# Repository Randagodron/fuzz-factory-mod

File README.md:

# fuzz-factory-mod
Heavily modified Fuzz Factory

Stompbox for electric guitar, based on the Fuzz Factory from ZVex, with digital control, HMI, preset memorisation and more.

This circuit is an experimentation platform around the Fuzz Face / Tonebender fuzz circuits.

# HW features

* Full-analog audio path, with digital control through digipots and VCAs
* Mono audio input and output, expression pedal input, MIDI in / out
* Standard stompbox DC power supply (9V, positive ring) + 9V battery
* 3 push button footwitches
* Multi-PCB, modular design with separated PCB for HMI and core audio circuit for future customisation
* Mechanical mounting through pots and audio connectors
* 4-Layer class 5 PCB for main board, 2-layer class 4 for HMI and audio circuit
* ...

# SW features

* STM32F303 MCU
* Preset memorisation via rolling EEPROM emulation inside MCU Flash memory
* MIDI support
* ...

# Contents

* Circuit CAD : Kicad
* Mechanics : FreeCAD
* Simulation : LTSpice
* SW : STM32CubeIDE

# Directory structure

* /cad : Kicad files
* /sim : electronics simulation files
* /mec : mechanical files
* /sw : software files
* /export : binaries and Kicad outputs

# Companion articles (in french)

http://blog.randagodron.eu/index.php?post/2019/05/26/Fuzzquest-Episode-2  
http://blog.randagodron.eu/index.php?post/2020/02/14/Fuzzquest-Episode-3  
http://blog.randagodron.eu/index.php?post/2020/03/26/Fuzzquest-Episode-4

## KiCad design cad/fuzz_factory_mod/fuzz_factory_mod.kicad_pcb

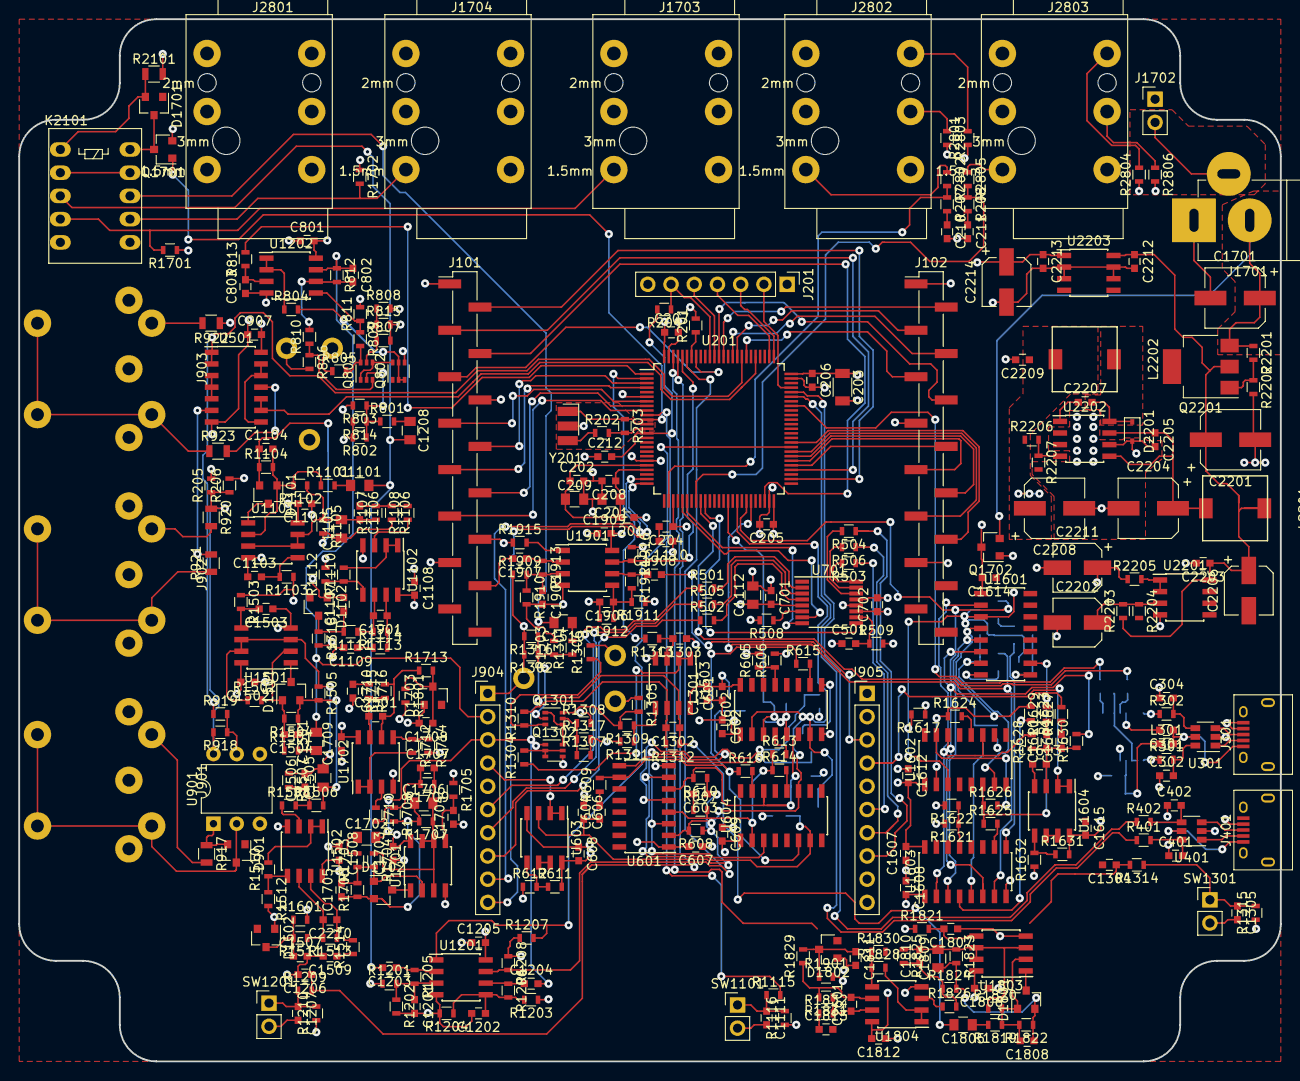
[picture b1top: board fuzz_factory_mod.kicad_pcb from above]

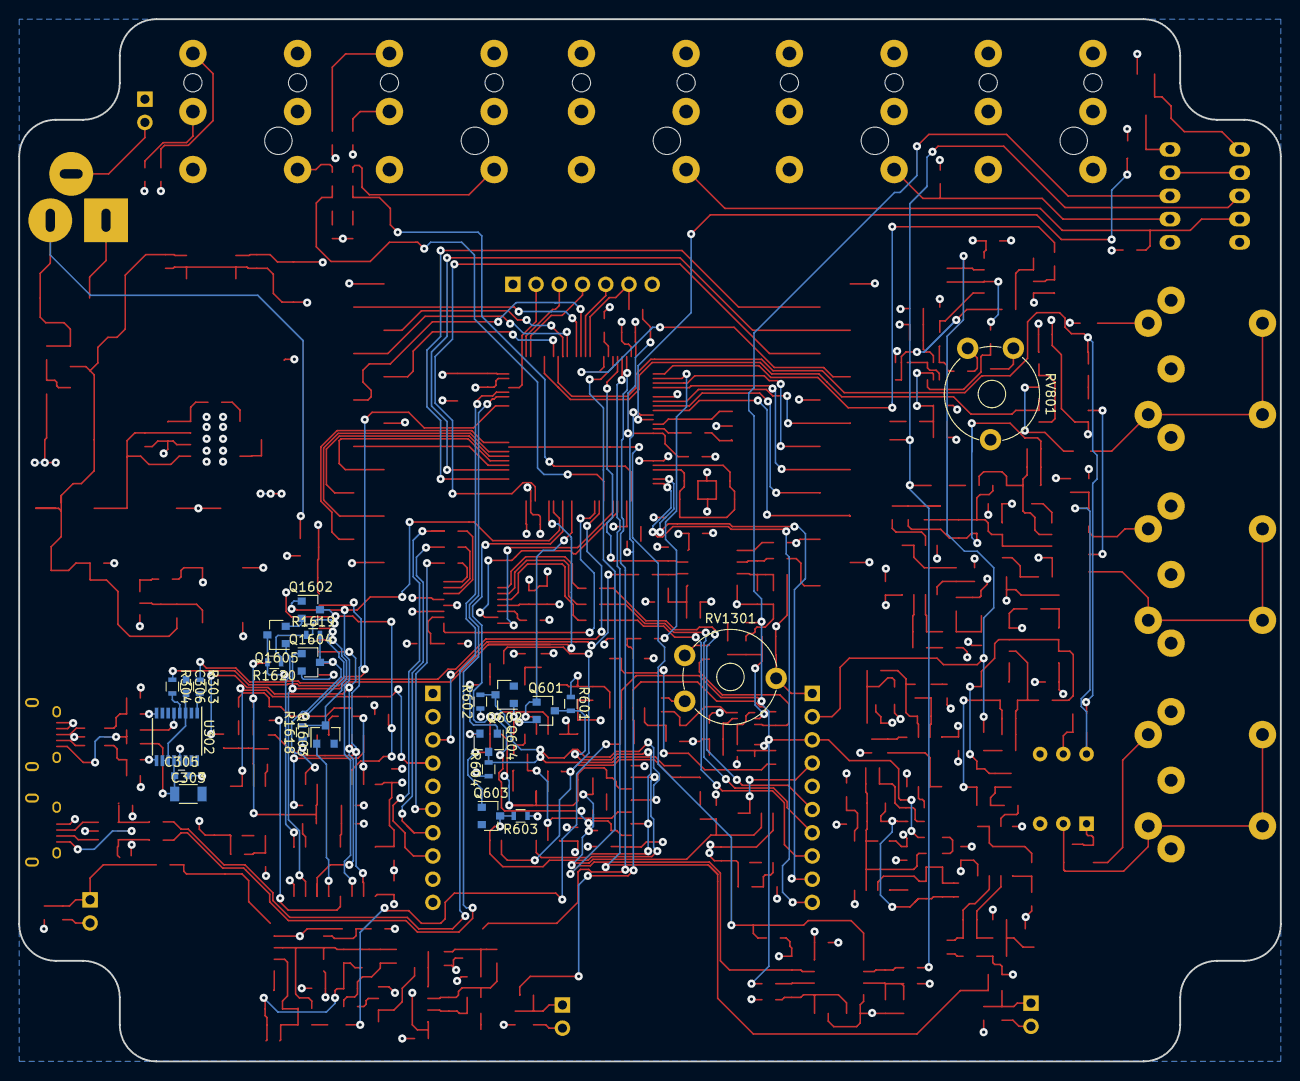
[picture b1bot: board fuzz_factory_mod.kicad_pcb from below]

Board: 4 copper layers, 138.0 x 114.0 mm, 388 parts (23 on the bottom side), 268 nets.

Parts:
C201, C209, C1101, C1112, C1208, C1501, C1510, C1702, C1805: 1u; C_0805
C202, C208, C301: 10n; C_0603
C203, C303: 4u7; C_1206
C204, C205, C206, C207, C210, C211, C212, C305, C306, C501, C601, C602, C603, C604, C606, C607, C608, C609, C701, C702, C801, C803, C907, C1102, C1103, C1104, C1106, C1107, C1108, C1109, C1110, C1111, C1201, C1202, C1203, C1204, C1205, C1206, C1207, C1301, C1303, C1304, C1305, C1502, C1503, C1504, C1506, C1507, C1508, C1509, C1607, C1608, C1609, C1610, C1612, C1613, C1614, C1615, C1703, C1704, C1705, C1707, C1708, C1709, C1710, C1806, C1807, C1808, C1810, C1811, C1812, C1813, C1905, C1906, C1907, C1908, C1909: 100n; C_0603
C302, C304, C401, C402: 47p; C_0603
C802, C1302, C1901, C2210, C2501, C2601: 100p; C_0603
C1105, C1505, C1706, C1809: 220n; C_0805
C1701, C2201, C2204, C2208: 100uF/25V; CP_Elec_6.3x4.5
C2202, C2206, C2211, C2214: 10u; CP_Elec_5x5.8
C2203, C2205, C2209, C2212, C2213: 100nF; C_0603
C2207: 10nF; C_0603
D901: BAT54A; SOT-23
D1101, D1501, D1701, D1702, D1801: BAV23S; SOT-23
D1102, D1502, D1703, D1802: BZX84Cxx; D_SOT-23_ANK
D2201: BAS3010B; D_SOD-323
J101: Conn_interface_1; Pin_Header_Straight_1x16_Pitch2.54mm_SMD_Pin1Left
J102: Conn_interface_2; Pin_Header_Straight_1x16_Pitch2.54mm_SMD_Pin1Left
J201: Conn_MCU_SWD; Pin_Header_Straight_1x07_Pitch2.54mm
J301, J401: USB_B_Micro; USB_Micro-B
J901: CONN_MIDI_IN; DIN5_through_hole
J902: CONN_MIDI_THRU; DIN5_through_hole
J903: CONN_MIDI_OUT; DIN5_through_hole
J904, J905: Conn_01x10_Female; Pin_Header_Straight_1x10_Pitch2.54mm
J1701: Barrel_Jack_Switch; JACK_ALIM
J1702: Conn_Battery; Pin_Header_Straight_1x02_Pitch2.54mm
J1703: CONN_AUDIO_IN; CLIFF_FCR5005x
J1704: CONN_AUDIO_OUT; CLIFF_FCR5005x
J2801: CONN_AUDIO_OUT_REF; CLIFF_FCR5005x
J2802: CONN_EXP_1; CLIFF_FCR5005x
J2803: CONN_EXP_2; CLIFF_FCR5005x
K2101: Fujitsu-Takamisawa-A_AL; Relay_DPDT_FRT5
L201: BLMxxx; C_0603
L301: L_Core_Ferrite_Small; C_0603
L2201, L2202: 100u; L_TDK_SLF7045
Q601, Q602, Q603, Q604, Q1602, Q1603, Q1604, Q1605: DTA123Y; SOT-23
Q801, Q802, Q1301, Q1302: MMDT3904; SOT-363_SC-70-6
Q1701: DTC114Y; SOT-23
Q1702: DTA114E; SOT-23
Q2201: BCP51; SOT-223
R201, R509, R611, R612, R803, R804, R808, R813, R814, R815, R1102, R1103, R1105, R1106, R1108, R1110, R1111, R1112, R1113, R1114, R1116, R1210, R1303, R1304, R1308, R1313, R1315, R1316, R1317, R1318, R1502, R1503, R1505, R1506, R1508, R1510, R1511, R1512, R1513, R1514, R1601, R1631, R1632, R1704, R1705, R1707, R1708, R1710, R1712, R1713, R1714, R1715, R1716, R1801, R1820, R1821, R1823, R1824, R1826, R1828, R1829, R1830, R1831, R1832, R1901, R2201, R2202, R2203, R2204: 10k; R_0603
R202: 390; R_0603
R203, R607, R608, R801, R1301, R1627, R1628, R1701, R1702: 1M; R_0603
R204, R205, R206, R501, R502, R503, R504, R505, R506, R508, R605, R606, R613, R614, R615, R616, R1621, R1622, R1623, R1624, R1625, R1626: 0; R_0603
R207, R208, R919, R1115, R1209, R1314, R2205: 100; R_0603
R301, R302, R303, R304, R401, R402: 27; R_0603
R601, R602, R603, R604, R918, R1201, R1202, R1203, R1204, R1617, R1618, R1619, R1620, R1909, R1910, R1911, R1912: 4k7; R_0603
R609, R610, R1629, R1630: 3k9; R_0603
R802, R807, R809, R810, R811, R812, R1104, R1107, R1205, R1206, R1302, R1307, R1309, R1310, R1311, R1312, R1504, R1507, R1706, R1709, R1822, R1825, R1913, R1914: 100k; R_0603
R805, R806, R1305, R1306: 330; R_0603
R917, R920, R921, R922, R923: 220; R_0805
R1101, R1207, R1208, R1501, R1703, R1819, R1915, R1916, R2801, R2802, R2803, R2804, R2805, R2806: 1k; R_0603
R2101: 200; R_0805
R2206: 82k; R_0603
R2207: 47k; R_0603
RV801, RV1301: R_POT_TRIM; Potentiometer_Trimmer_Piher_PT-10v10_Horizontal_Px10.0mm_Py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
SW1101, SW1201, SW1301: SW_PUSH; Pin_Header_Straight_1x02_Pitch2.54mm
U201: STM32F303VCTx; LQFP-100_14x14mm_Pitch0.5mm
U301, U401: USBLC6-2SC6; SOT-23-6
U302: FT230XS; SSOP-16_3.9x4.9mm_Pitch0.635mm
U501: 74LS132; SOIC-14_3.9x8.7mm_Pitch1.27mm
U601, U1601: 4050; SOIC-16_3.9x9.9mm_Pitch1.27mm
U602, U1603: 4504; SOIC-16_3.9x9.9mm_Pitch1.27mm
U603, U1102, U1202, U1502, U1503, U1604, U1702, U1804: MC33202; SOIC-8_3.9x4.9mm_Pitch1.27mm
U604, U1602: 4049; SOIC-16_3.9x9.9mm_Pitch1.27mm
U701: AD5262_ABC; TSSOP-16_4.4x5mm_Pitch0.65mm
U901: 4N25; DIP-6_W7.62mm
U1101, U1501, U1701, U1803: LM1458; SOIC-8_3.9x4.9mm_Pitch1.27mm
U1201, U1901: LM2903; SOIC-8_3.9x4.9mm_Pitch1.27mm
U2201: TL072; SOIC-8_3.9x4.9mm_Pitch1.27mm
U2202: LM2674M-ADJ; SOIC-8_3.9x4.9mm_Pitch1.27mm
U2203: LM78L05_SO8; SOIC-8_3.9x4.9mm_Pitch1.27mm
Y201: Resonator_Small; Resonator_AEL_ZTTxx_SMD

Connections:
+3.3VA: C201.1, C202.1, C208.1, C209.1, L201.2, U201.21, U201.22
+3V3: C203.1, C204.1, C205.1, C206.1, C207.1, C602.2, C702.2, C1608.2, C2208.1, C2209.1, J101.12, J102.7, J201.1, L201.1, L2202.2, R205.2, R508.2, R509.2, R605.2, R1116.1, R1207.1, R1208.1, R1210.1, R1315.1, R1621.2, R1915.1, R1916.1, R2206.1, R2801.1, R2804.1, U201.6, U201.28, U201.50, U201.75, U201.100, U602.1, U701.13, U1603.1
+5V: C2213.1, C2214.1, J101.6, R206.2, U2203.1
+9V: C601.2, C607.2, C608.2, C609.2, C701.2, C801.2, C1102.2, C1108.2, C1112.1, C1205.2, C1301.2, C1502.2, C1508.2, C1607.2, C1612.2, C1614.2, C1615.2, C1703.2, C1709.2, C1806.2, C1812.2, C1909.2, J904.1, J905.1, Q1702.3, R601.1, R602.1, R603.1, R604.1, R611.2, R802.2, R807.2, R811.2, R814.2, R815.2, R1201.1, R1203.1, R1302.2, R1307.2, R1311.2, R1316.2, R1317.2, R1318.2, R1601.2, R1617.1, R1618.1, R1619.1, R1620.1, R1631.2, R1801.2, R1901.2, R1909.1, R1911.1, RV801.2, RV1301.2, U601.1, U602.16, U603.8, U604.1, U701.5, U1101.8, U1102.8, U1201.8, U1202.8, U1501.8, U1502.8, U1503.8, U1601.1, U1602.1, U1603.16, U1604.8, U1701.8, U1702.8, U1803.8, U1804.8, U1901.8
+BATT: C1701.1, J1701.2, Q1702.2, Q2201.3, R2101.2, R2201.1
/ANALOG/DAC/IN_PWM_LSB_BUFF: R608.2, U601.2, U602.2, U604.11
/ANALOG/DAC/IN_PWM_LSBn: Q602.1, U602.5
/ANALOG/DAC/IN_PWM_LSBn_BUFF: R607.2, R613.1, R614.1, U601.4, U604.2
/ANALOG/DAC/IN_PWM_MSB_BUFF: R610.2, U601.6, U602.6, U604.14
/ANALOG/DAC/IN_PWM_MSBn: Q604.1, U602.9
/ANALOG/DAC/IN_PWM_MSBn_BUFF: R609.2, R615.1, R616.1, U601.10, U604.6
/ANALOG/DAC_CMD: J904.4, U603.1, U603.2
/ANALOG/DAC_CMD_REF: J905.4, U1604.1, U1604.2
/ANALOG/DAC_REF/IN_PWM_LSB_BUFF: R1628.2, U1601.2, U1602.11, U1603.2
/ANALOG/DAC_REF/IN_PWM_LSBn: Q1603.1, U1603.5
/ANALOG/DAC_REF/IN_PWM_LSBn_BUFF: R1623.1, R1624.1, R1627.2, U1601.4, U1602.2
/ANALOG/DAC_REF/IN_PWM_MSB_BUFF: R1630.2, U1601.6, U1602.14, U1603.6
/ANALOG/DAC_REF/IN_PWM_MSBn: Q1605.1, U1603.9
/ANALOG/DAC_REF/IN_PWM_MSBn_BUFF: R1625.1, R1626.1, R1629.2, U1601.10, U1602.6
/ANALOG/Digipot/POT1_1: R501.2, U701.2
/ANALOG/Digipot/POT1_2: R505.2, U701.3
/ANALOG/Digipot/POT1_3: R502.2, U701.4
/ANALOG/Digipot/POT2_1: R503.2, U701.16
/ANALOG/Digipot/POT2_2: R506.2, U701.15
/ANALOG/Digipot/POT2_3: R504.2, U701.14
/ANALOG/Digipot/~DIGIPOT_PR: C501.2, R509.1, U701.10
/ANALOG/Digipot/~DIGIPOT_SHDN: R508.1, U701.6
/ANALOG/GAIN_POT_1: J904.6, R501.1
/ANALOG/GAIN_POT_2: J904.7, R505.1
/ANALOG/GAIN_POT_3: J904.8, R502.1
/ANALOG/GAIN_POT_REF_1: J905.6, R503.1
/ANALOG/GAIN_POT_REF_2: J905.7, R506.1
/ANALOG/GAIN_POT_REF_3: J905.8, R504.1
/ANALOG/IN_AUDIO_PEAK: C1109.1, R1114.1
/ANALOG/IN_AUDIO_VCA: C802.1, C1501.2, J904.2, R812.1, U1202.7
/ANALOG/IN_AUDIO_VCA_PEAK: C1509.1, R1514.1
/ANALOG/OUT_AUDIO_PEAK: C1710.1, R1716.1
/ANALOG/OUT_AUDIO_REF: C1908.2, J905.3
/ANALOG/OUT_AUDIO_VCA_PEAK: C1813.1, R1832.1
/ANALOG/VCA_IN/CV: C803.2, R813.1, U1202.3
/ANALOG/VCA_OUT/CV: C1303.2, R1313.1, U1503.3
/ANALOG/freq_meas_ref/OUT_1: R1915.2, U1901.1
/ANALOG/peak_detect_audio_in/Vsub: C1107.1, D1102.1, R1111.2, R1318.1
/ANALOG/peak_detect_in_audio_vca/Vsub: C1507.1, D1502.1, R1511.2, R1601.1
/ANALOG/peak_detect_out_audio/Vsub: C1708.1, D1703.1, R1713.2, R1801.1
/ANALOG/peak_detect_out_audio_vca/Vsub: C1811.1, D1802.1, R1829.2, R1901.1
/CONNECTORS/AUDIO_IN_CONN: J1703.3, K2101.4, R1701.2
/CONNECTORS/AUDIO_OUT_CONN: J1704.3, K2101.7, R1702.2
/MCU/JNTRST: J201.6, R204.1, U201.90
/MCU/JTCK_SWCLK: J201.3, U201.76
/MCU/JTDI: J201.4, U201.77
/MCU/JTDO_TRACESWO: J201.5, U201.89
/MCU/JTMS_SWDIO: J201.2, U201.72
/MCU/MIDI/+5V_IN: C907.2, R205.1, R206.1, R918.2, R920.1, R922.1, U501.14, U901.6
/MCU/NRST: C212.2, R204.2, U201.14
/MCU/SW_BYPASS: C1110.1, R1115.2, U201.10
/MCU/SW_PRESET_DOWN: C1304.1, R1314.2, U201.98
/MCU/SW_PRESET_UP: C1206.1, R1209.2, U201.97
/MCU/UART5_RX: R919.1, U201.83, U501.1, U501.2
/MCU/UART5_TX: U201.80, U501.9, U501.10
/MCU/USART1_RX: R304.1, U201.34
/MCU/USART1_TX: R303.1, U201.68
/MCU/USB_UART/VBUS: C303.1, C305.1, L301.1, U302.12
/PSU/DCDC_VSW: C2207.2, D2201.1, L2202.1, U2202.8
ADC_FF_pol1: J904.9, U201.24
ADC_FF_pol2: J904.10, U201.25
AUDIO_IN_FX: C1101.2, C1203.2, C1208.2, K2101.3
AUDIO_OUT_FX: C1204.2, C1302.1, C1510.2, C1702.2, C1805.2, J904.3, K2101.8, R1312.1, U1503.7
BYPASS_CMD: Q1701.1, U201.11
DISP_ENABLE: J101.4, U201.48
DISP_LATCH: J101.5, U201.93
ENC1_BTN: J101.7, U201.7
ENC1_IN_CCW: J101.11, U201.9
ENC1_IN_CW: J101.10, U201.8
ENC1__LED_GREEN: J101.9, U201.4
ENC1__LED_RED: J101.8, U201.3
ENC2_BTN: J102.2, U201.87
ENC2_IN_CCW: J102.6, U201.88
ENC2_IN_CW: J102.5, U201.82
ENC2_LED_GREEN: J102.4, U201.85
ENC2_LED_RED: J102.3, U201.84
ENC3_BTN: J102.8, U201.55
ENC3_IN_CCW: J102.12, U201.60
ENC3_IN_CW: J102.11, U201.58
ENC3_LED_GREEN: J102.10, U201.57
ENC3_LED_RED: J102.9, U201.56
EXP_1: R207.1, R2802.2, U201.27
EXP_2: R208.1, R2805.2, U201.33
FF_Stab_DAC_PWM_LSB: Q601.1, U201.40, U602.3
FF_Stab_DAC_PWM_MSB: Q603.1, U201.42, U602.7
GNDA: C201.2, C202.2, C203.2, C204.2, C205.2, C206.2, C207.2, C208.2, C209.2, C210.2, C211.2, C212.1, C301.2, C302.1, C303.2, C304.1, C305.2, C306.1, C401.1, C402.1, C501.1, C601.1, C602.1, C606.1, C607.1, C608.1, C609.1, C701.1, C702.1, C801.1, C803.1, C907.1, C1102.1, C1103.1, C1107.2, C1108.1, C1109.2, C1110.2, C1111.2, C1112.2, C1201.2, C1202.2, C1205.1, C1206.2, C1207.2, C1301.1, C1303.1, C1304.2, C1305.2, C1502.1, C1503.1, C1507.2, C1508.1, C1509.2, C1607.1, C1608.1, C1612.1, C1613.1, C1614.1, C1615.1, C1701.2, C1703.1, C1704.1, C1708.2, C1709.1, C1710.2, C1806.1, C1807.1, C1811.2, C1812.1, C1813.2, C1905.2, C1906.2, C1909.1, C2201.2, C2202.2, C2203.2, C2204.2, C2205.2, C2206.2, C2208.2, C2209.2, C2211.2, C2212.2, C2213.2, C2214.2, D1102.2, D1502.2, D1703.2, D1802.2, D2201.2, J101.1, J101.13, J102.1, J102.13, J201.7, J301.4, J301.5, J301.6, J401.4, J401.5, J401.6, J902.2, J903.2, J904.5, J905.5, J1701.1, J1703.1, J1703.4, J1704.1, J1704.4, J2801.1, J2801.4, J2802.1, J2802.6, J2803.1, J2803.6, Q601.2, Q602.2, Q603.2, Q604.2, Q802.1, Q802.4, Q1302.1, Q1302.4, Q1602.2, Q1603.2, Q1604.2, Q1605.2, Q1701.2, Q1702.1, R201.2, R606.2, R612.1, R803.2, R808.2, R1112.2, R1202.2, R1204.2, R1303.2, R1308.2, R1512.2, R1622.2, R1632.1, R1701.1, R1702.1, R1714.2, R1830.2, R1910.2, R1912.2, R2202.2, R2204.2, R2207.2, R2803.2, R2806.2, SW1101.2, SW1201.2, SW1301.2, U201.20, U201.49, U201.74, U201.99, U301.2, U302.5, U302.13, U401.2, U501.7, U601.8, U602.8, U603.4, U604.8, U701.11, U701.12, U901.4, U1101.4, U1102.4, U1201.4, U1202.4, U1501.4, U1502.4, U1503.4, U1601.8, U1602.8, U1603.8, U1604.4, U1701.4, U1702.4, U1803.4, U1804.4, U1901.4, U2201.4, U2202.6, U2203.2, U2203.3, U2203.6, U2203.7, Y201.2
INPUT_CAPTURE_1: R1207.2, U201.59, U1201.1
INPUT_CAPTURE_2: R1208.2, U201.95, U1201.7
INPUT_CAPTURE_3: R1916.2, U201.96, U1901.7
unnamed: C210.1, R207.2
unnamed: C211.1, R208.2
unnamed: C301.1, J301.1, L301.2, U301.5
unnamed: C302.2, R301.2, U301.6
unnamed: C304.2, R302.2, U301.4
unnamed: C306.2, U302.3, U302.10, U302.11
unnamed: C401.2, R401.2, U401.6
unnamed: C402.2, R402.2, U401.4
unnamed: C603.1, C604.1, C606.2, R608.1, R610.1, U603.3
unnamed: C603.2, R607.1
unnamed: C604.2, R609.1
unnamed: C802.2, R810.2, R812.2, U1202.6
unnamed: C1101.1, R1101.2
unnamed: C1103.2, R1103.2, U1101.5
unnamed: C1104.1, C1105.1, D1101.2, R1104.1, R1105.2, R1106.2
unnamed: C1104.2, D1101.1, R1101.1, R1102.2, R1104.2, U1101.2
unnamed: C1105.2, C1106.2, R1102.1, R1105.1, R1107.1, U1101.3, U1101.6, U1101.7
unnamed: C1106.1, R1106.1, R1107.2, R1108.2
unnamed: C1111.1, R1115.1, R1116.2, SW1101.1
unnamed: C1201.1, R1201.2, R1202.1, R1205.2, U1201.3
unnamed: C1202.1, R1203.2, R1204.1, R1206.2, U1201.5
unnamed: C1203.1, R1205.1, U1201.2
unnamed: C1204.1, R1206.1, U1201.6
unnamed: C1207.1, R1209.1, R1210.2, SW1201.1
unnamed: C1208.1, R801.2
unnamed: C1302.2, R1310.2, R1312.2, U1503.6
unnamed: C1305.1, R1314.1, R1315.2, SW1301.1
unnamed: C1501.1, R1501.2
unnamed: C1503.2, R1503.2, U1501.5
unnamed: C1504.1, C1505.1, D1501.2, R1504.1, R1505.2, R1506.2
unnamed: C1504.2, D1501.1, R1501.1, R1502.2, R1504.2, U1501.2
unnamed: C1505.2, C1506.2, R1502.1, R1505.1, R1507.1, U1501.3, U1501.6, U1501.7
unnamed: C1506.1, R1506.1, R1507.2, R1508.2
unnamed: C1510.1, R1301.2
unnamed: C1609.1, C1610.1, C1613.2, R1628.1, R1630.1, U1604.3
unnamed: C1609.2, R1627.1
unnamed: C1610.2, R1629.1
unnamed: C1702.1, R1703.2
unnamed: C1704.2, R1705.2, U1701.5
unnamed: C1705.1, C1706.1, D1702.2, R1706.1, R1707.2, R1708.2
unnamed: C1705.2, D1702.1, R1703.1, R1704.2, R1706.2, U1701.2
unnamed: C1706.2, C1707.2, R1704.1, R1707.1, R1709.1, U1701.3, U1701.6, U1701.7
unnamed: C1707.1, R1708.1, R1709.2, R1710.2
unnamed: C1805.1, R1819.2
unnamed: C1807.2, R1821.2, U1803.5
unnamed: C1808.1, C1809.1, D1801.2, R1822.1, R1823.2, R1824.2
unnamed: C1808.2, D1801.1, R1819.1, R1820.2, R1822.2, U1803.2
unnamed: C1809.2, C1810.2, R1820.1, R1823.1, R1825.1, U1803.3, U1803.6, U1803.7
unnamed: C1810.1, R1824.1, R1825.2, R1826.2
unnamed: C1901.1, R1113.1, R1114.2, U1102.7
unnamed: C1901.2, R1111.1, R1113.2, U1102.6
unnamed: C1905.1, R1909.2, R1910.1, R1913.2, U1901.3
unnamed: C1906.1, R1911.2, R1912.1, R1914.2, U1901.5
unnamed: C1907.1, R1913.1, U1901.2
unnamed: C1908.1, R1914.1, U1901.6
unnamed: C2201.1, C2203.1, C2206.1, C2212.1, L2201.1, Q2201.2, R2203.1, U2201.8, U2203.8
unnamed: C2202.1, R2203.2, R2204.1, U2201.3
unnamed: C2204.1, C2205.1, L2201.2, U2202.5, U2202.7
unnamed: C2207.1, U2202.1
unnamed: C2210.1, R1513.1, R1514.2, U1502.7
unnamed: C2210.2, R1511.1, R1513.2, U1502.6
unnamed: C2501.1, R1715.1, R1716.2, U1702.7
unnamed: C2501.2, R1713.1, R1715.2, U1702.6
unnamed: C2601.1, R1831.1, R1832.2, U1804.7
unnamed: C2601.2, R1829.1, R1831.2, U1804.6
unnamed: D901.2, R917.1, U901.1
unnamed: D901.3, J901.5, U901.2
unnamed: D1101.3, U1101.1
unnamed: D1501.3, U1501.1
unnamed: D1701.2, K2101.1, R2101.1
unnamed: D1701.3, K2101.10, Q1701.3
unnamed: D1702.3, U1701.1
unnamed: D1801.3, U1803.1
unnamed: J301.2, U301.1
unnamed: J301.3, U301.3
unnamed: J401.1, U401.5
unnamed: J401.2, U401.1
unnamed: J401.3, U401.3
unnamed: J901.4, R917.2
unnamed: J902.4, R920.2
unnamed: J902.5, R921.1
unnamed: J903.4, R922.2
unnamed: J903.5, R923.1
unnamed: J1701.3, J1702.2
unnamed: J1702.1, J1703.5
unnamed: J2802.3, R2802.1
unnamed: J2802.4, R2801.2
unnamed: J2802.5, R2803.1
unnamed: J2803.3, R2805.1
unnamed: J2803.4, R2804.2
unnamed: J2803.5, R2806.1
unnamed: K2101.2, K2101.9
unnamed: Q601.3, R601.2, U601.3, U604.3
unnamed: Q602.3, R602.2, U601.5
unnamed: Q603.3, R603.2, U601.7, U604.7
unnamed: Q604.3, R604.2, U601.9
unnamed: Q801.1, Q801.4, Q802.6
unnamed: Q801.2, R801.1, R802.1, R803.1, R814.1
unnamed: Q801.3, R806.1, R810.1
unnamed: Q801.5, R807.1, R808.1, R815.1
unnamed: Q801.6, R805.2, R809.2
unnamed: Q802.2, Q802.3, Q802.5, R804.2
unnamed: Q1301.1, Q1301.4, Q1302.6
unnamed: Q1301.2, R1301.1, R1302.1, R1303.1, R1316.1
unnamed: Q1301.3, R1306.1, R1310.1
unnamed: Q1301.5, R1307.1, R1308.1, R1317.1
unnamed: Q1301.6, R1305.2, R1309.2
unnamed: Q1302.2, Q1302.3, Q1302.5, R1304.2
unnamed: Q1602.3, R1617.2, U1601.3, U1602.3
unnamed: Q1603.3, R1618.2, U1601.5
unnamed: Q1604.3, R1619.2, U1601.7, U1602.7
unnamed: Q1605.3, R1620.2, U1601.9
unnamed: Q2201.1, R2201.2, R2202.1
unnamed: R201.1, U201.94
unnamed: R202.1, Y201.3
unnamed: R202.2, R203.2, U201.13
unnamed: R203.1, U201.12, Y201.1
unnamed: R301.1, U302.9
unnamed: R302.1, U302.8
unnamed: R303.2, U302.1
unnamed: R304.2, U302.4
unnamed: R605.1, R606.1, U602.13
unnamed: R611.1, R612.2, U603.5
unnamed: R613.2, U602.4
unnamed: R614.2, U604.12
unnamed: R615.2, U602.10
unnamed: R616.2, U604.15
unnamed: R804.1, U1202.1, U1202.2
unnamed: R805.1, RV801.1
unnamed: R806.2, RV801.3
unnamed: R809.1, R811.1, U1202.5
unnamed: R918.1, R919.2, U901.5
unnamed: R921.2, U501.6
unnamed: R923.2, U501.11
unnamed: R1108.1, U1102.3
unnamed: R1110.1, R1112.1, U1102.5
unnamed: R1110.2, U1102.1, U1102.2
unnamed: R1304.1, U1503.1, U1503.2
unnamed: R1305.1, RV1301.1
unnamed: R1306.2, RV1301.3
unnamed: R1309.1, R1311.1, U1503.5
unnamed: R1508.1, U1502.3
unnamed: R1510.1, R1512.1, U1502.5
unnamed: R1510.2, U1502.1, U1502.2
unnamed: R1621.1, R1622.1, U1603.13
unnamed: R1623.2, U1603.4
unnamed: R1624.2, U1602.12
unnamed: R1625.2, U1603.10
unnamed: R1626.2, U1602.15
unnamed: R1631.1, R1632.2, U1604.5
unnamed: R1710.1, U1702.3
unnamed: R1712.1, R1714.1, U1702.5
unnamed: R1712.2, U1702.1, U1702.2
unnamed: R1826.1, U1804.3
unnamed: R1828.1, R1830.1, U1804.5
unnamed: R1828.2, U1804.1, U1804.2
unnamed: R2205.2, U2201.1, U2201.2
unnamed: R2206.2, R2207.1, U2202.4
unnamed: U501.3, U501.4, U501.5
unnamed: U501.8, U501.12, U501.13
unnamed: U603.6, U603.7
unnamed: U1604.6, U1604.7
Ref_Stab_DAC_PWM_LSB: Q1602.1, U201.44, U1603.3
Ref_Stab_DAC_PWM_MSB: Q1604.1, U201.45, U1603.7
SPI2_MOSI: J101.3, U201.54
SPI2_SCK: J101.2, U201.52
SPI_FF_Gain_CS: U201.35, U701.9
SPI_FF_Gain_MISO: U201.31, U701.8
SPI_FF_Gain_SCK: U201.30, U701.7
USB_DM: R401.1, U201.70
USB_DP: R402.1, U201.71
VCA_IN_PWM: R813.2, U201.1
VCA_OUT_PWM: R1313.2, U201.2
VCOM: C2211.1, R1103.1, R1503.1, R1705.1, R1821.1, R2205.1

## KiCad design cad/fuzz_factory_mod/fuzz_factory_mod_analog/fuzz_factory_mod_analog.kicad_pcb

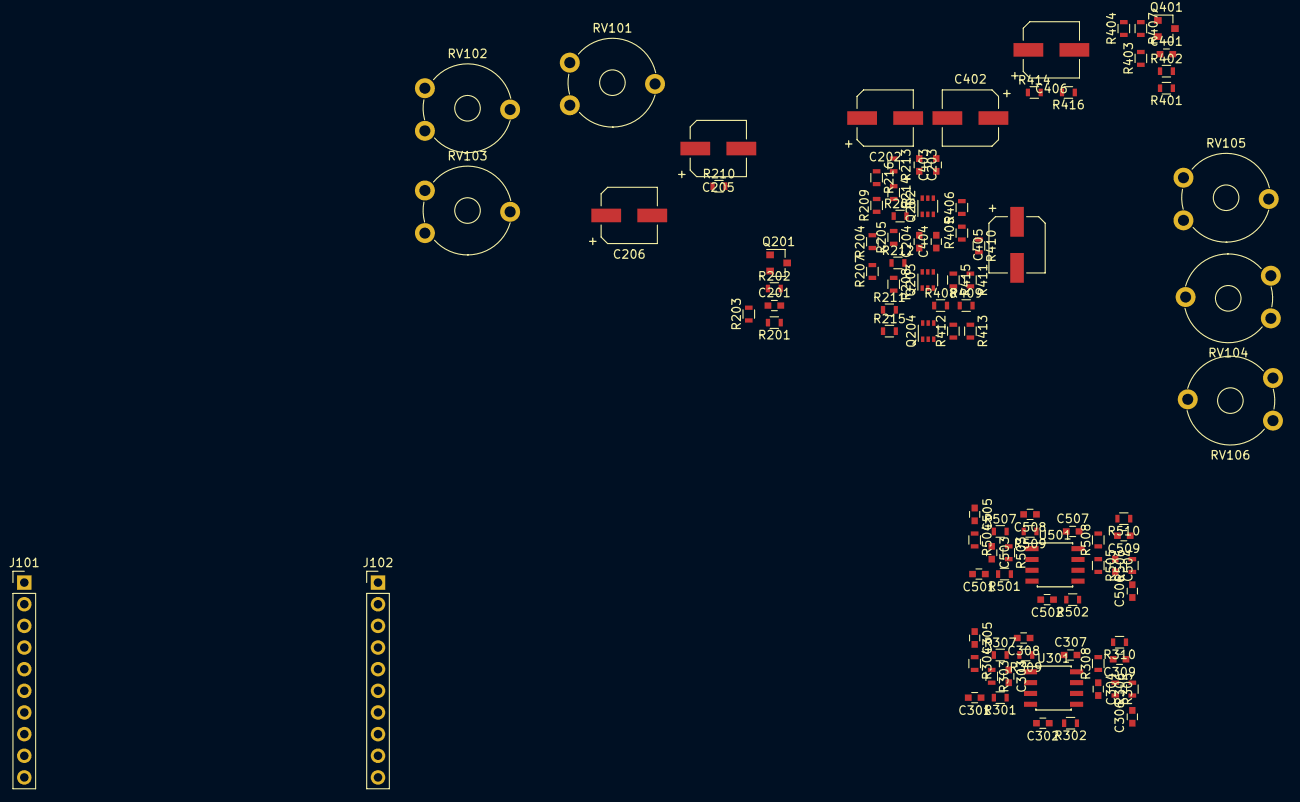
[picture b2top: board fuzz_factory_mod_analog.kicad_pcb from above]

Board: 2 copper layers, 97 parts (0 on the bottom side), 62 nets, no tracks yet.

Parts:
C201, C308, C309, C401, C508, C509: 10n; C_0603
C202, C205, C206, C402, C405, C406: 10u; CP_Elec_6.3x4.5
C203, C204, C301, C302, C305, C306, C307, C403, C404, C501, C502, C505, C506, C507: 100n; C_0603
C303, C304, C503, C504: 100p; C_0603
J101, J102: Conn_01x10_Male; Pin_Header_Straight_1x10_Pitch2.54mm
Q201, Q401: Q_NJFET_DSG; SOT-23
Q202: DMMT3904W; SOT-363_SC-70-6
Q203, Q204: DMMT3906W; SOT-363_SC-70-6
R201, R301, R302, R401, R501, R502: 1k; R_0603
R202, R402: 51k; R_0603
R203, R204, R303, R305, R403, R404, R503, R505: 0; R_0603
R205, R209, R210, R211, R215, R304, R306, R307, R308, R405, R409, R410, R411, R415, R504, R506, R507, R508: 10k; R_0603
R206, R216, R406, R416: 220k; R_0603
R207, R213, R214, R407, R413, R414: 4k7; R_0603
R208, R408: 470; R_0603
R212, R412: 5k1; R_0603
R309, R310, R509, R510: 3k3; R_0603
RV101: TRIM_VOLUME; Potentiometer_Trimmer_Piher_PT-10v10_Horizontal_Px10.0mm_Py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
RV102: TRIM_COMP; Potentiometer_Trimmer_Piher_PT-10v10_Horizontal_Px10.0mm_Py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
RV103: TRIM_GATE; Potentiometer_Trimmer_Piher_PT-10v10_Horizontal_Px10.0mm_Py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
RV104: TRIM_VOLUME_REF; Potentiometer_Trimmer_Piher_PT-10v10_Horizontal_Px10.0mm_Py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
RV105: TRIM_COMP_REF; Potentiometer_Trimmer_Piher_PT-10v10_Horizontal_Px10.0mm_Py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
RV106: TRIM_GATE_REF; Potentiometer_Trimmer_Piher_PT-10v10_Horizontal_Px10.0mm_Py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
U301, U501: MC33202; SOIC-8_3.9x4.9mm_Pitch1.27mm

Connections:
+9V: C307.2, J101.1, J102.1, R203.1, R403.1, U301.8
/DAC_CMD: J101.4, R201.2
/DAC_CMD_REF: J102.4, R401.2
/GAIN_POT_1: C205.1, J101.6, Q203.1, R204.2, R205.1, R210.1, R215.1, RV102.3
/GAIN_POT_2: C205.2, J101.7, R210.2, R211.1
/GAIN_POT_3: J101.8, Q204.1, R211.2, R215.2, RV102.1, RV102.2
/GAIN_POT_REF_1: C405.1, J102.6, Q203.4, R404.2, R405.1, R410.1, R415.1, RV105.3
/GAIN_POT_REF_2: C405.2, J102.7, R410.2, R411.1
/GAIN_POT_REF_3: J102.8, Q204.4, R411.2, R415.2, RV105.1, RV105.2
/IN_AUDIO_REF: C402.2, C403.1, J102.2
/IN_AUDIO_VCA: C202.2, C203.1, J101.2
/OUT_AUDIO: C206.2, J101.3, R216.1
/OUT_AUDIO_REF: C406.2, J102.3, R416.1
/fuzz_factory/GATE_POT_1: R208.2, R209.1, RV103.3
/fuzz_factory/POL_MEAS_1: C204.2, C301.2, Q202.6, R205.2, R206.1
/fuzz_factory/POL_MEAS_2: C204.1, C302.2, Q203.2
/fuzz_factory/STARVE_POT_1: C201.1, Q201.1, R202.1, R203.2, R207.1
/fuzz_factory/STARVE_POT_2: Q201.2, R204.1, R207.2
/fuzz_factory/VOLUME_POT_1: R212.2, R213.1, RV101.3
/fuzz_factory/VOLUME_POT_2: C206.1, R213.2, R214.1, RV101.2
/fuzz_factory_ref/ADC_frontend_2/GND: C505.1, C506.1, C507.1, C508.1, C509.1, R509.1, R510.1, U501.4
/fuzz_factory_ref/ADC_frontend_2/VCC: C507.2, U501.8
/fuzz_factory_ref/GATE_POT_1: R408.2, R409.1, RV106.3
/fuzz_factory_ref/POL_MEAS_1: C404.2, C501.2, Q202.3, R405.2, R406.1
/fuzz_factory_ref/POL_MEAS_2: C404.1, C502.2, Q203.5
/fuzz_factory_ref/STARVE_POT_1: C401.1, Q401.1, R402.1, R403.2, R407.1
/fuzz_factory_ref/STARVE_POT_2: Q401.2, R404.1, R407.2
/fuzz_factory_ref/VOLUME_POT_1: R412.2, R413.1, RV104.3
/fuzz_factory_ref/VOLUME_POT_2: C406.1, R413.2, R414.1, RV104.2
ADC_FF_pol1: C308.2, J101.9, R307.2, R309.2
ADC_FF_pol2: C309.2, J101.10, R308.2, R310.2
ADC_REF_pol1: C508.2, J102.9, R507.2, R509.2
ADC_REF_pol2: C509.2, J102.10, R508.2, R510.2
GNDA: C305.1, C306.1, C307.1, C308.1, C309.1, J101.5, J102.5, Q202.1, Q202.4, R209.2, R214.2, R216.2, R309.1, R310.1, R409.2, R414.2, R416.2, RV101.1, RV103.1, RV103.2, RV104.1, RV106.1, RV106.2, U301.4
unnamed: C201.2, Q201.3, R201.1, R202.2
unnamed: C202.1, C203.2, Q202.2, R206.2
unnamed: C301.1, R301.2
unnamed: C302.1, R302.2
unnamed: C303.1, R303.1, R304.2, R307.1, U301.1
unnamed: C303.2, R303.2, U301.2
unnamed: C304.1, R305.1, R306.2, R308.1, U301.7
unnamed: C304.2, R305.2, U301.6
unnamed: C305.2, R304.1
unnamed: C306.2, R306.1
unnamed: C401.2, Q401.3, R401.1, R402.2
unnamed: C402.1, C403.2, Q202.5, R406.2
unnamed: C501.1, R501.2
unnamed: C502.1, R502.2
unnamed: C503.1, R503.1, R504.2, R507.1, U501.1
unnamed: C503.2, R503.2, U501.2
unnamed: C504.1, R505.1, R506.2, R508.1, U501.7
unnamed: C504.2, R505.2, U501.6
unnamed: C505.2, R504.1
unnamed: C506.2, R506.1
unnamed: Q203.3, Q204.5, R408.1
unnamed: Q203.6, Q204.2, R208.1
unnamed: Q204.3, R412.1
unnamed: Q204.6, R212.1
unnamed: R301.1, U301.3
unnamed: R302.1, U301.5
unnamed: R501.1, U501.3
unnamed: R502.1, U501.5

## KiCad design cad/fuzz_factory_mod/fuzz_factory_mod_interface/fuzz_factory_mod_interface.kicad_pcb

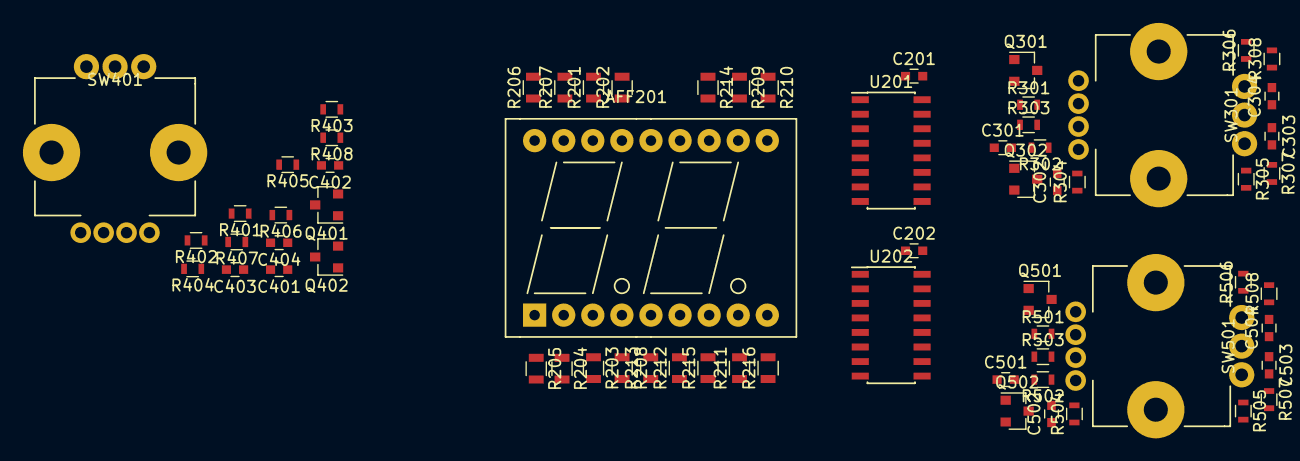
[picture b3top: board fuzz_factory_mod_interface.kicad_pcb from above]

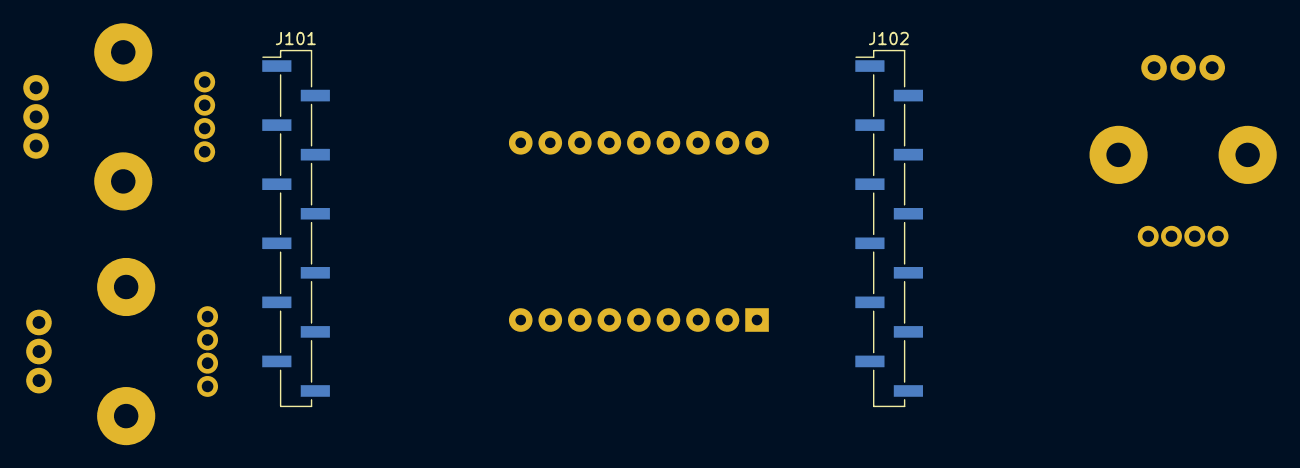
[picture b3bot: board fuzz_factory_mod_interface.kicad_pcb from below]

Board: 2 copper layers, 68 parts (2 on the bottom side), 70 nets, no tracks yet.

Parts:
AFF201: HDSP-521E; AFF_2x7SEG-PT-DIGIT_10mm
C201, C202, C301, C302, C303, C304, C401, C402, C403, C404, C501, C502, C503, C504: 100n; C_0603
J101, J102: Conn_01x12_Male; Pin_Header_Straight_1x12_Pitch2.54mm_SMD_Pin1Left
Q301, Q302, Q401, Q402, Q501, Q502: DTA123Y; SOT-23
R201, R202, R203, R204, R205, R206, R207, R208, R209, R210, R211, R212, R213, R214, R215, R216: 470; R_0805
R301, R303, R304, R305, R306, R401, R403, R404, R405, R406, R501, R503, R504, R505, R506: 10k; R_0603
R302, R307, R308, R402, R407, R408, R502, R507, R508: 100; R_0603
SW301, SW401, SW501: PEL12D-4225S-S2024; PEL12D
U201, U202: TLC6C598-Q1; SOIC-16_3.9x9.9mm_Pitch1.27mm

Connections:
+3V3: J101.12, J102.7, R304.1, R305.2, R306.2, R404.1, R405.2, R406.2, R504.1, R505.2, R506.2
+5V: AFF201.13, AFF201.14, C201.2, C202.2, J101.6, R301.1, R303.1, R401.1, R403.1, R501.1, R503.1, U201.10, U201.16, U202.10, U202.16
/DISP_ENABLE: J101.4, U201.13, U202.13
/DISP_LATCH: J101.5, U201.12, U202.12
/ENC1_BTN: C301.2, J101.7, R302.2
/ENC1_IN_CCW: C303.2, J101.11, R307.1
/ENC1_IN_CW: C304.2, J101.10, R308.1
/ENC1_LED_GREEN: J101.9, Q301.1
/ENC1_LED_RED: J101.8, Q302.1
/ENC2_BTN: C401.2, J102.2, R402.2
/ENC2_IN_CCW: C403.2, J102.6, R407.1
/ENC2_IN_CW: C404.2, J102.5, R408.1
/ENC2_LED_GREEN: J102.4, Q401.1
/ENC2_LED_RED: J102.3, Q402.1
/ENC3_BTN: C501.2, J102.8, R502.2
/ENC3_IN_CCW: C503.2, J102.12, R507.1
/ENC3_IN_CW: C504.2, J102.11, R508.1
/ENC3_LED_GREEN: J102.10, Q501.1
/ENC3_LED_RED: J102.9, Q502.1
/SPI2_MOSI: J101.3, U201.14
/SPI2_SCK: J101.2, U201.11, U202.11
/interface/shift1_data_out_int: U201.9, U202.14
GNDD: C201.1, C202.1, C301.1, C302.1, C303.1, C304.1, C401.1, C402.1, C403.1, C404.1, C501.1, C502.1, C503.1, C504.1, J101.1, J102.1, Q301.2, Q302.2, Q401.2, Q402.2, Q501.2, Q502.2, SW301.1, SW301.C, SW401.1, SW401.C, SW501.1, SW501.C, U201.8, U202.8
unnamed: AFF201.1, R205.1
unnamed: AFF201.2, R204.1
unnamed: AFF201.3, R203.1
unnamed: AFF201.4, R208.1
unnamed: AFF201.5, R213.2
unnamed: AFF201.6, R212.2
unnamed: AFF201.7, R215.2
unnamed: AFF201.8, R211.2
unnamed: AFF201.9, R216.2
unnamed: AFF201.10, R210.2
unnamed: AFF201.11, R209.2
unnamed: AFF201.12, R214.2
unnamed: AFF201.15, R202.1
unnamed: AFF201.16, R201.1
unnamed: AFF201.17, R207.1
unnamed: AFF201.18, R206.1
unnamed: C302.2, R302.1, R304.2, SW301.4
unnamed: C402.2, R402.1, R404.2, SW401.4
unnamed: C502.2, R502.1, R504.2, SW501.4
unnamed: Q301.3, R301.2, SW301.2
unnamed: Q302.3, R303.2, SW301.3
unnamed: Q401.3, R401.2, SW401.2
unnamed: Q402.3, R403.2, SW401.3
unnamed: Q501.3, R501.2, SW501.2
unnamed: Q502.3, R503.2, SW501.3
unnamed: R201.2, U201.15
unnamed: R202.2, U201.1
unnamed: R203.2, U201.2
unnamed: R204.2, U201.3
unnamed: R205.2, U201.4
unnamed: R206.2, U201.5
unnamed: R207.2, U201.6
unnamed: R208.2, U201.7
unnamed: R209.1, U202.15
unnamed: R210.1, U202.1
unnamed: R211.1, U202.2
unnamed: R212.1, U202.3
unnamed: R213.1, U202.4
unnamed: R214.1, U202.5
unnamed: R215.1, U202.6
unnamed: R216.1, U202.7
unnamed: R305.1, R307.2, SW301.A
unnamed: R306.1, R308.2, SW301.B
unnamed: R405.1, R407.2, SW401.A
unnamed: R406.1, R408.2, SW401.B
unnamed: R505.1, R507.2, SW501.A
unnamed: R506.1, R508.2, SW501.B

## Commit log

2019-12-01 Added components on schematic.
2019-12-12 Added simulation file for DAC + FF.
    Continued schematic.
2019-12-13 Continued schematic
2019-12-26 Continued schematic.
    Added PSU and interface from tremolo project.
2020-03-08 Factorised fuzz factory circuit.
    Added MIDI interface.
2020-03-09 Added peak detector.
    Added ADC frontend module.
2020-03-26 Modified OPA repartition on peak detector.
2020-05-02 Continued schematic.
    Modified fuuz_factory circuit : use of matched transistor pairs.
    Added USB interface, through FT230X and direct to MCU.
    Associated footprints, except for XTAL and trimmers.
2020-05-22 Continued schematic.
2020-05-31 Continued schematic.
    Continued component placement.
2020-05-31 Added drawing for stacking.
2020-06-02 Commit pre- board separation.
2020-07-26 Changes architecture.
    Corrections on schematic.
    Continued Layout placement.
2020-07-26 Continued layout placement.
2020-09-01 Updated trimmers footprint.
    Continued layout.
2020-10-03 Continued layout.
2020-10-21 Continued layout. Started power planes.
2020-10-26 Layout continued : finished power polys on internal layer.
2020-10-31 Layout finished : 0 unrouted, to be cleaned.
2021-01-01 Created README.md
2021-01-01 Update README.md.
